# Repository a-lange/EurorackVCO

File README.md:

WIP!
Not functional, might pick this up later or replace the core of the oscillator!
As my first layout project, I bit over more than I could chew.

# EurorackVCO
Clone of Befaco 'even' VCO, original files (accessed 2025-12-12):
https://befaco.org/docs/Even_VCO/

The original pcb states that the design is public domain. Their website says CC-NC-SA.

This projects goal is to remake the 'Even VCO' in a 8hp format, to be ordered on a PCBA service like JLCPCB.
Files are (for now) easyeda pro.

First prototypes has been ordered

Sorry about the ugly pictures:

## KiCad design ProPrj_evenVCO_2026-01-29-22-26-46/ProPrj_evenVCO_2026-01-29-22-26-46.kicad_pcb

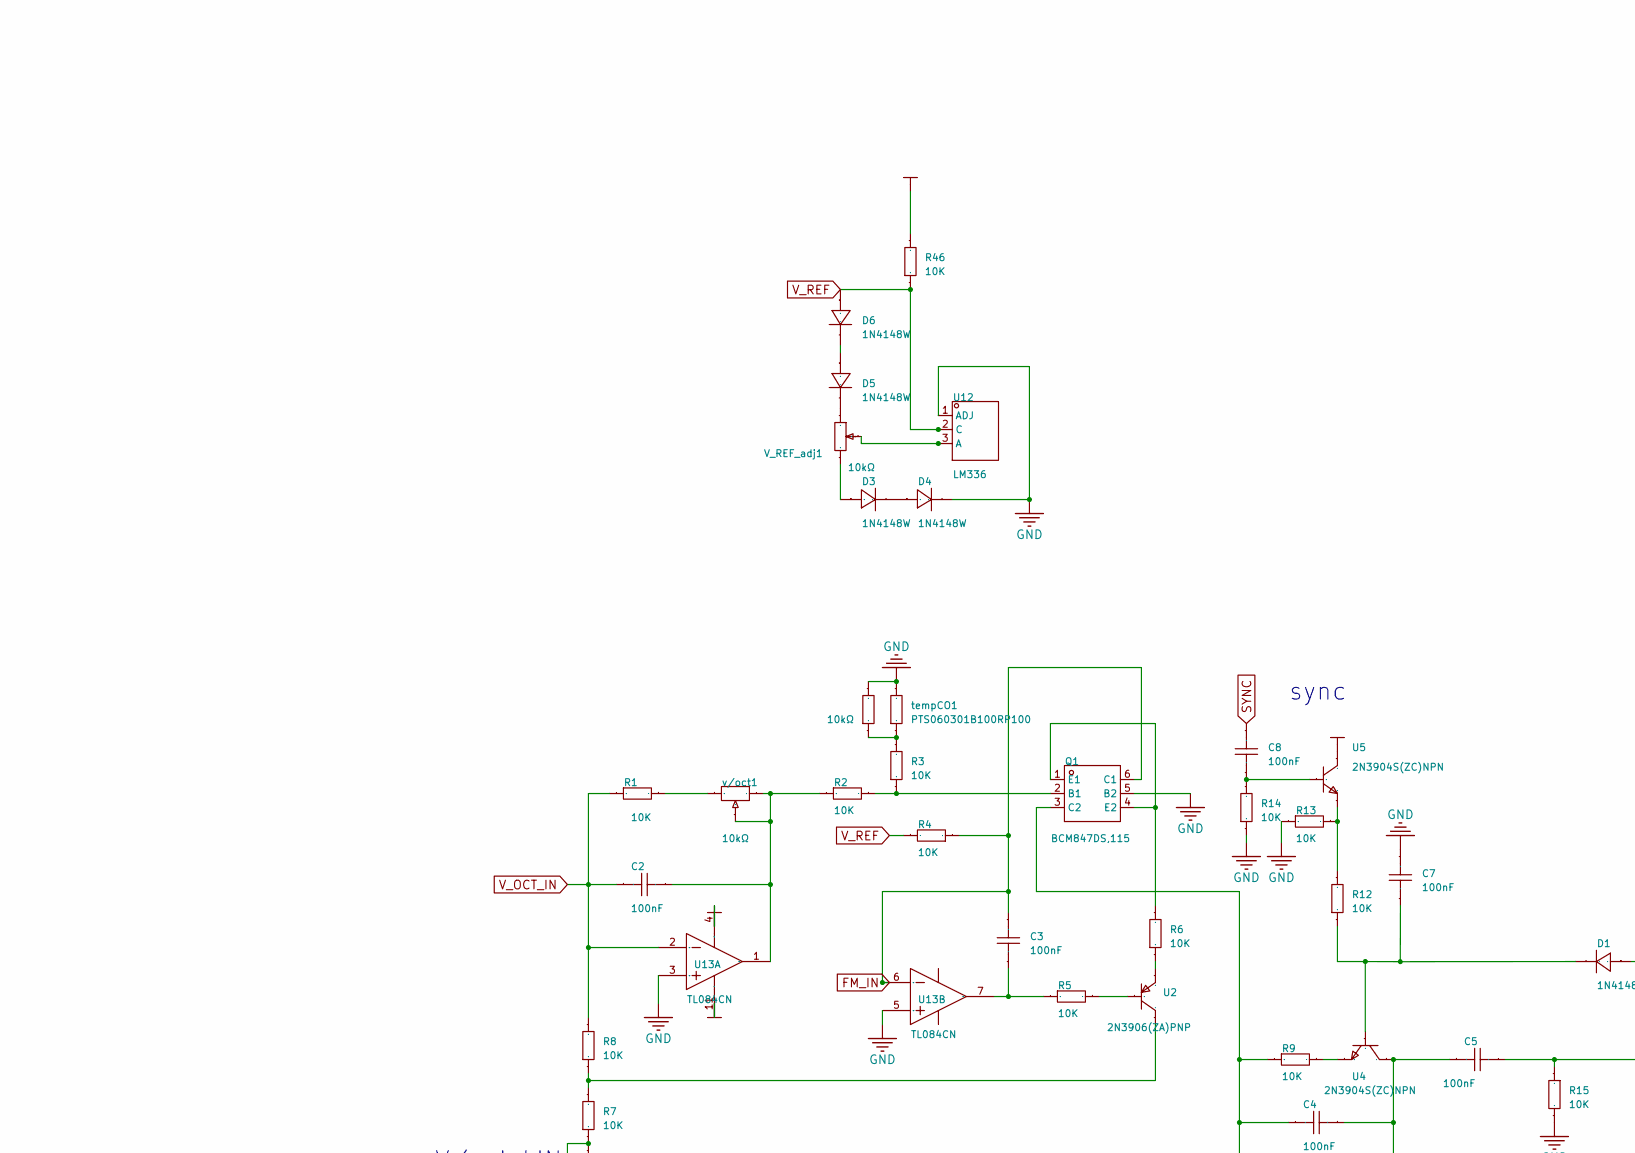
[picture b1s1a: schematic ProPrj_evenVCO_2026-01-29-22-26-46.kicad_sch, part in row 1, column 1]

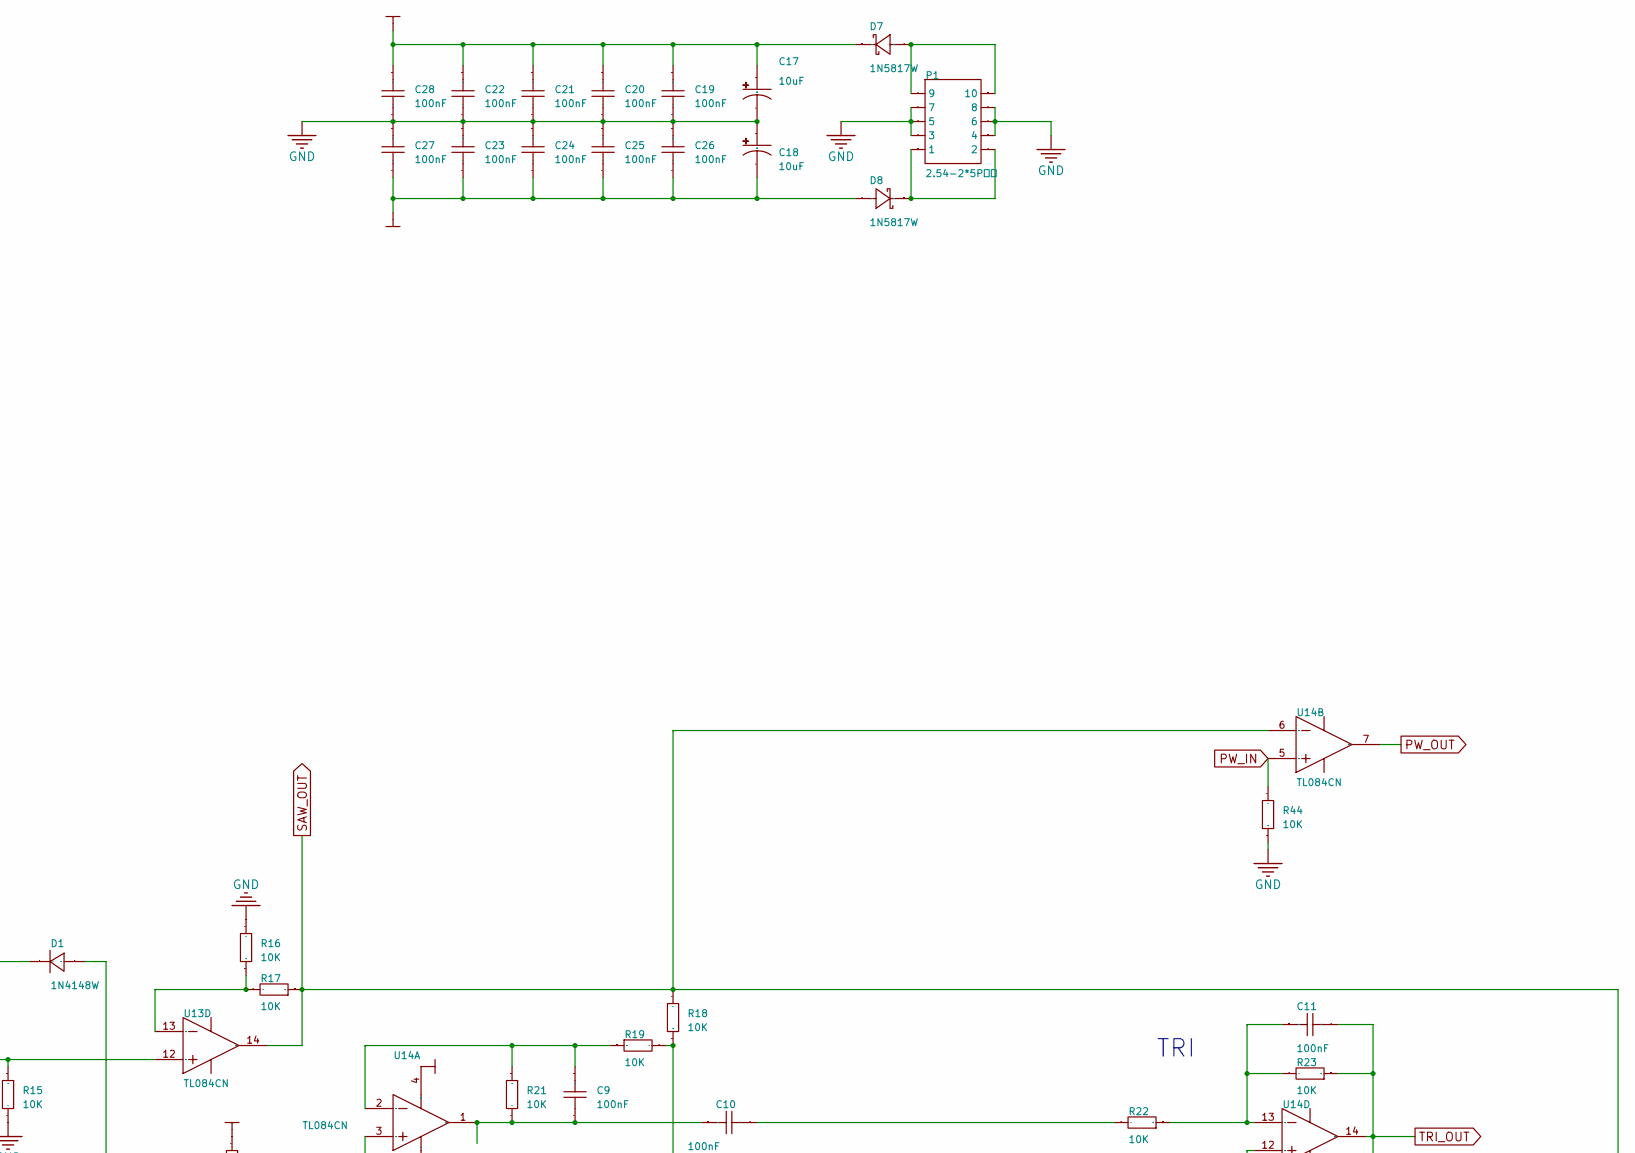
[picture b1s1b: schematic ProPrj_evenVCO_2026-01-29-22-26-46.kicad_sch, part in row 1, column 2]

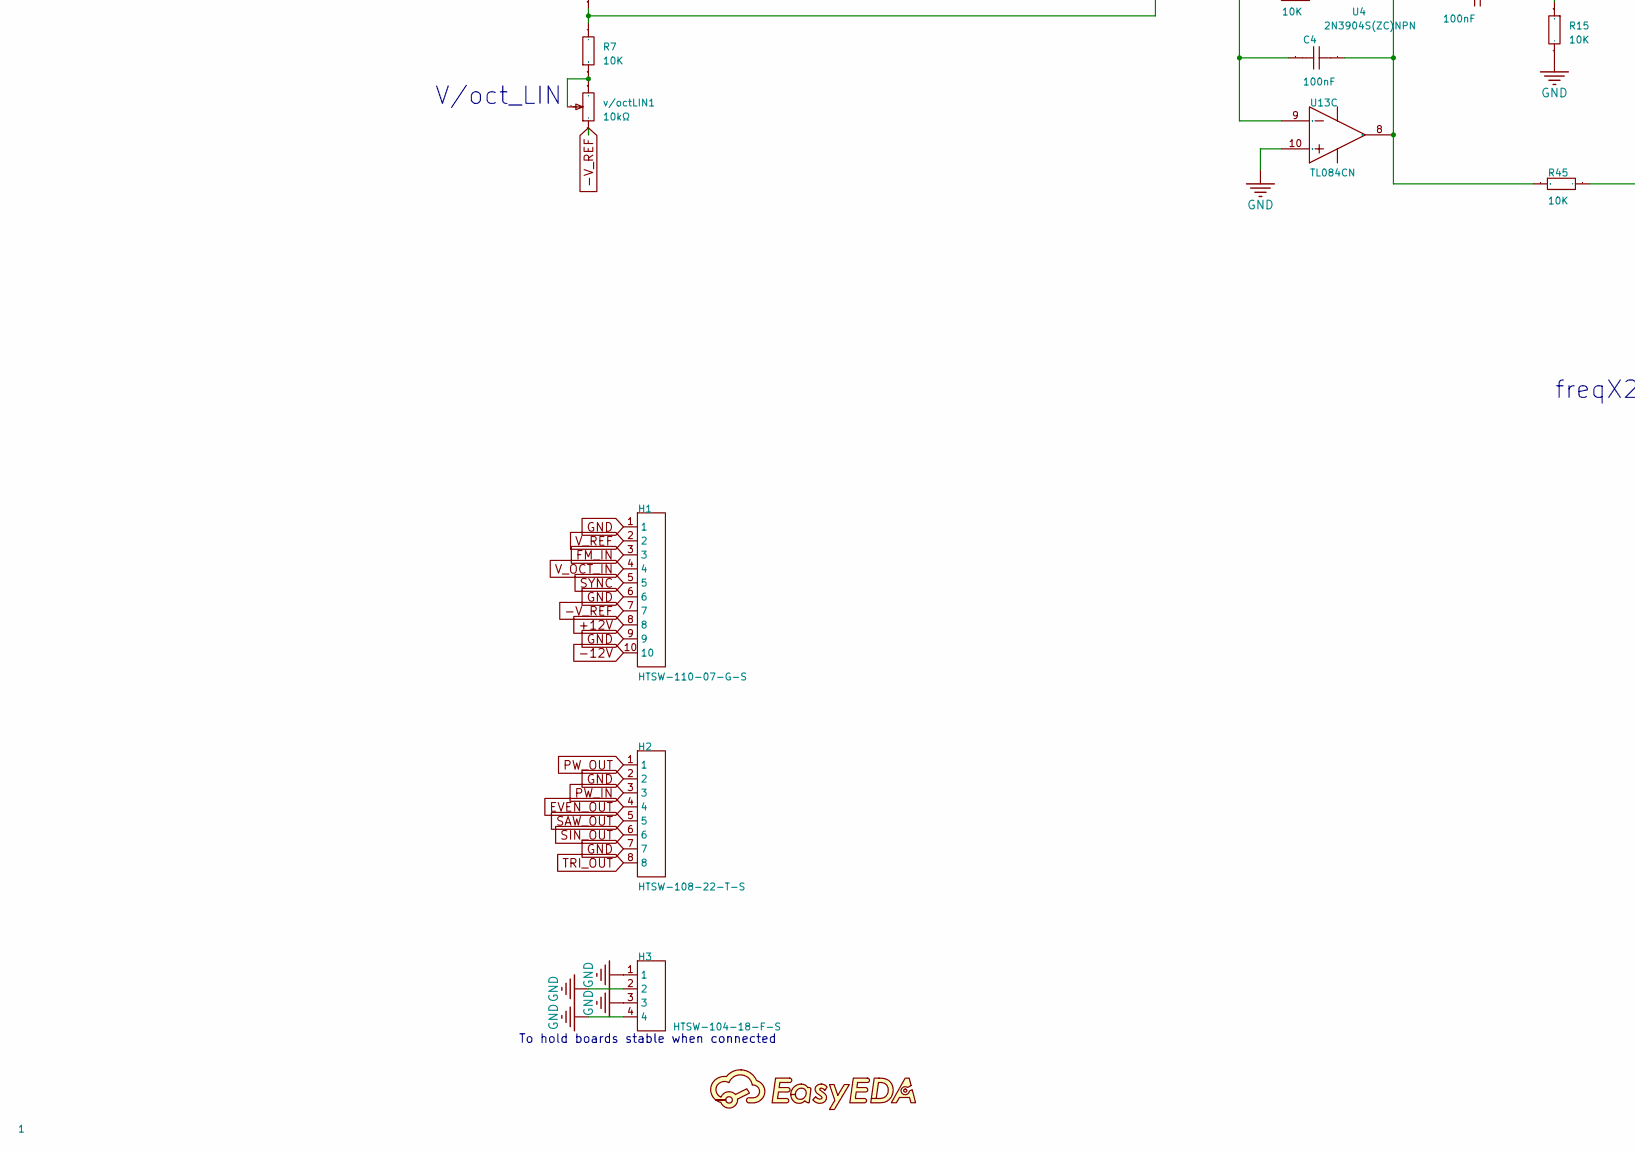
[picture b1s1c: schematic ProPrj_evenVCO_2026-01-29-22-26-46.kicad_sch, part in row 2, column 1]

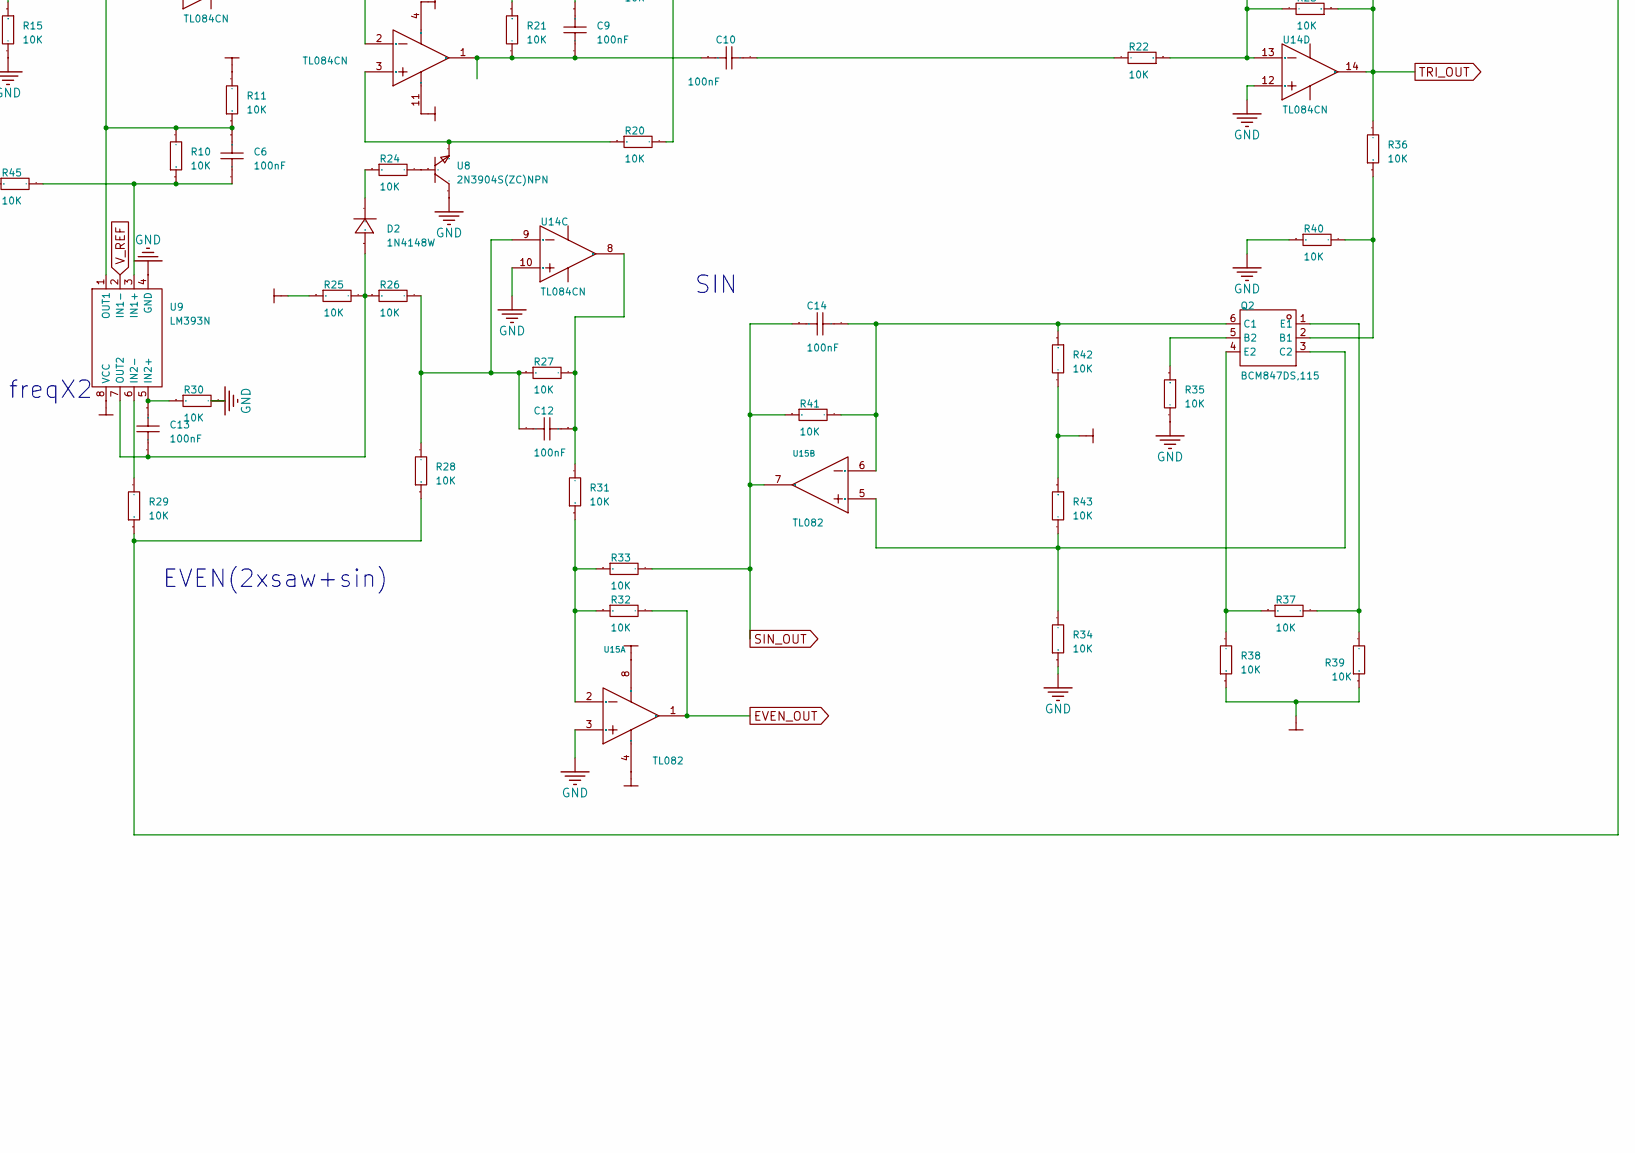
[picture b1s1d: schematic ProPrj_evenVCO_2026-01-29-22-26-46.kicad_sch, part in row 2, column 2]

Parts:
1: (no value)
C2, C3, C4, C5, C6, C7, C8, C9, C10, C11, C12, C13, C14, C19, C20, C21, C22, C23, C24, C25, C26, C27, C28: 100nF; C0805
C17, C18: 10uF; CAP-TH_BD10.0-P5.00-D1.0-FD-H16.0; Manufacturer Part 450BXW10MEFR10X16; LCSC Part Name 10uF ±20% 450V
D1, D2, D3, D4, D5, D6: 1N4148W; DO-35_BD2.0-L4.2-P8.20-D0.5-R-RD; Manufacturer Part 1N4148W; LCSC Part Name 1N4148W
D7, D8: 1N5817W; DO-41_BD2.4-L4.7-P8.70-D0.8-RD; Manufacturer Part 1N5817W; LCSC Part Name 电压:20V 电流:1A
H1: HTSW-110-07-G-S; HDR-TH_TSW-110-17-F-S-LL; Manufacturer Part HTSW-110-07-G-S; LCSC Part Name 间距:2.54mm 直插
H2: HTSW-108-22-T-S; HDR-TH_HTSW-108-22-T-S; Manufacturer Part HTSW-108-22-T-S; LCSC Part Name 间距:2.54mm 直插
H3: HTSW-104-18-F-S; HDR-TH_HTSW-104-25-S-S-LL; Manufacturer Part HTSW-104-18-F-S; LCSC Part Name 间距:2.54mm 直插
P1: 2.54-2*5P简牛; IDC-TH_10P-P2.54_C5665; Manufacturer Part power; LCSC Part Name 2.54mm 2x5P 排数:2 每排P数:5
Q1, Q2: BCM847DS,115; SC-74-6_L2.9-W1.5-P0.95-LS2.8-BR; Manufacturer Part BCM847DS,115; LCSC Part Name NPN 电流:100mA 电压:45V
R1, R2, R3, R4, R5, R6, R7, R8, R9, R10, R11, R12, R13, R14, R15, R16, R17, R18, R19, R20, R21, R22, R23, R24, R25, R26, R27, R28, R29, R30, R31, R32, R33, R34, R35, R36, R37, R38, R39, R40, R41, R42, R43, R44, R45, R46: 10K; R0805
RTemp1: 10kΩ; R0805
U2: 2N3906(ZA)PNP; SOT-23-3_L2.9-W1.3-P0.95-LS2.4-BR; Manufacturer Part 2N3906(ZA)PNP; LCSC Part Name 2N3906(ZA)PNP
U4, U5, U8: 2N3904S(ZC)NPN; SOT-23-3_L2.9-W1.3-P0.95-LS2.4-BR; Manufacturer Part 2N3904S(ZC)NPN; LCSC Part Name 2N3904S(ZC)NPN
U9: LM393N; DIP-8_L9.7-W6.4-P2.54-LS7.6-BL; Manufacturer Part LM393N; LCSC Part Name 双路差分比较器
U12: LM336; TO-92-3_L4.9-W3.7-P1.27-L; Manufacturer Part LM336; LCSC Part Name LM336
U13, U14: TL084CN; SOIC-14_L8.7-W3.9-P1.27-LS6.0-BL; Manufacturer Part TL084CN; LCSC Part Name JFET输入运算放大器
U15: TL082; SOP-8_L4.9-W3.9-P1.27-LS6.0-BL; Manufacturer Part TL082; LCSC Part Name TL082
V_REF_adj1: 10kΩ; RES-ADJ-TH_3P-L10.0-W10.0-P2.50-L
tempCO1: PTS060301B100RP100; R0805; Manufacturer Part PTS060301B100RP100; LCSC Part Name 铂金SMD扁平芯片温度传感器
v/oct1: 10kΩ; RES-ADJ-TH_3P_L9.6-W4.8-P2.50-L; Manufacturer Part CT-94EW103; LCSC Part Name 10kΩ ±10%
v/octLIN1: 10kΩ; RES-ADJ-TH_3P-L10.0-W10.0-P2.50-L

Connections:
$1N507: R1.2, v/oct1.3; also elsewhere on the board
$1N1389: C3.1, R5.1, U13.7 (OUT2)
$1N1507: R5.2, U2.2 (B)
$1N1586: R6.1, U2.1 (E)
$1N1640: R7.2, R8.1, U2.3 (C)
$1N1719: R7.1, v/octLIN1.1, v/octLIN1.2; also elsewhere on the board
$1N2016: C4.1, Q1.3 (C2), R9.1, U13.9 (IN3-)
$1N2204: R9.2, U4.2 (E)
$1N2447: C6.1, D1.1 (A), R10.2, R11.1, U9.1 (OUT1)
$1N2683: C5.1, R15.1, U13.12 (IN4+)
$1N2690: R3.2, RTemp1.1, tempCO1.1; also elsewhere on the board
$1N2936: Q1.1 (E1), Q1.4 (E2), R6.2
$1N2959: Q1.2 (B1), R2.2, R3.1
$1N3116: C4.2, C5.2, R45.1, U4.3 (C), U13.8 (OUT3)
$1N3938: C8.2, R14.2, U5.1 (B)
$1N3981: R12.2, R13.2, U5.2 (E)
$1N4358: R16.1, R17.2, U13.13 (IN4-)
$1N4747: R20.1, U8.2 (E), U14.3 (IN1+)
$1N4955: R18.1, R19.2, R20.2
$1N5308: C11.1, R22.1, R23.2, U14.13 (IN4-)
$1N5674: R24.2, U8.1 (B)
$1N5714: D2.2 (C), R24.1
$1N6127: C6.2, R10.1, R45.2, U9.3 (IN1+)
$1N6419: R29.2, U9.6 (IN2-)
$1N6424: C13.1, R30.1, U9.5 (IN2+)
$1N6566: C13.2, D2.1 (A), R25.2, R26.1, U9.7 (OUT2)
$1N7314: Q2.2 (B1), R36.1, R40.2
$1N7370: Q2.4 (E2), R37.1, R38.2
$1N7375: Q2.1 (E1), R37.2, R39.2
$1N8230: D3.1 (A), V_REF_adj1.1; also elsewhere on the board
$1N8312: U12.3 (A); also elsewhere on the board
$1N8440: D3.2 (C), D4.1 (A)
$1N8647: D5.1 (A), D6.2 (C)
$1N8687: D5.2 (C), V_REF_adj1.3; also elsewhere on the board
$1N9074: D8.1 (K), P1.1, P1.2
$1N9101: D7.2 (A), P1.9, P1.10
$1N9891: C2.1, R2.1, U13.1 (OUT1), v/oct1.1, v/oct1.2; also elsewhere on the board
$1N10311: C9.2, C10.1, R21.2, U14.1 (OUT1)
$1N10325: C9.1, R19.1, R21.1, U14.2 (IN1-)
$1N10403: C12.2, R26.2, R27.1, R28.2, U14.9 (IN3-)
$1N10523: C10.2, R22.2
$1N10728: Q2.3 (C2), R34.2, R43.2, U15.5 (2IN+)
$1N10768: C14.2, Q2.6 (C1), R41.2, R42.1, U15.6 (2IN-)
$1N10882: R31.1, R32.1, R33.1, U15.2 (1IN-)
$1N10889: C12.1, R27.2, R31.2, U14.8 (OUT3)
$1N11135: Q2.5 (B2), R35.1
+12V: C17.1, C19.1, C20.1, C21.1, C22.1, C28.1, D7.1 (K), H1.8, R11.2, R25.1, R42.2, R43.1, R46.2, U5.3 (C), U9.8 (VCC), U13.4 (VCC+), U14.4 (VCC+), U15.8 (VCC+)
-12V: C18.2, C23.2, C24.2, C25.2, C26.2, C27.2, D8.2 (A), H1.10, R38.1, R39.1, U13.11 (VCC-), U14.11 (VCC-), U15.4 (VCC-)
-V_REF: H1.7, v/octLIN1.3; also elsewhere on the board
EVEN_OUT: H2.4, R32.2, U15.1 (1OUT)
FM_IN: C3.2, H1.3, Q1.6 (C1), R4.1, U13.6 (IN2-)
GND: C7.1, C17.2, C18.1, C19.2, C20.2, C21.2, C22.2, C23.1, C24.1, C25.1, C26.1, C27.1, C28.2, D4.2 (C), H1.1, H1.6, H1.9, H2.2, H2.7, H3.1, H3.2, H3.3, H3.4, P1.3, P1.4, P1.5, P1.6, P1.7, P1.8, Q1.5 (B2), R13.1, R14.1, R15.2, R16.2, R30.2, R34.1, R35.2, R40.1, R44.1, RTemp1.2, U8.3 (C), U9.4 (GND), U12.1 (ADJ), U13.3 (IN1+), U13.5 (IN2+), U13.10 (IN3+), U14.10 (IN3+), U14.12 (IN4+), U15.3 (1IN+), tempCO1.2; also elsewhere on the board
PW_IN: H2.3, R44.2, U14.5 (IN2+)
PW_OUT: H2.1, U14.7 (OUT2)
SAW_OUT: H2.5, R17.1, R18.2, R28.1, R29.1, U13.14 (OUT4), U14.6 (IN2-)
SIN_OUT: C14.1, H2.6, R33.2, R41.1, U15.7 (2OUT)
SYNC: C8.1, H1.5
TRI_OUT: C11.2, H2.8, R23.1, R36.2, U14.14 (OUT4)
V_OCT_IN: C2.2, H1.4, R1.1, R8.2, U13.2 (IN1-)
V_REF: D6.1 (A), H1.2, R4.2, R46.1, U9.2 (IN1-), U12.2 (C)

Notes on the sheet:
freqX2
To hold boards stable when connected
sync
V/oct_LIN
SIN
TRI
EVEN(2xsaw+sin)

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
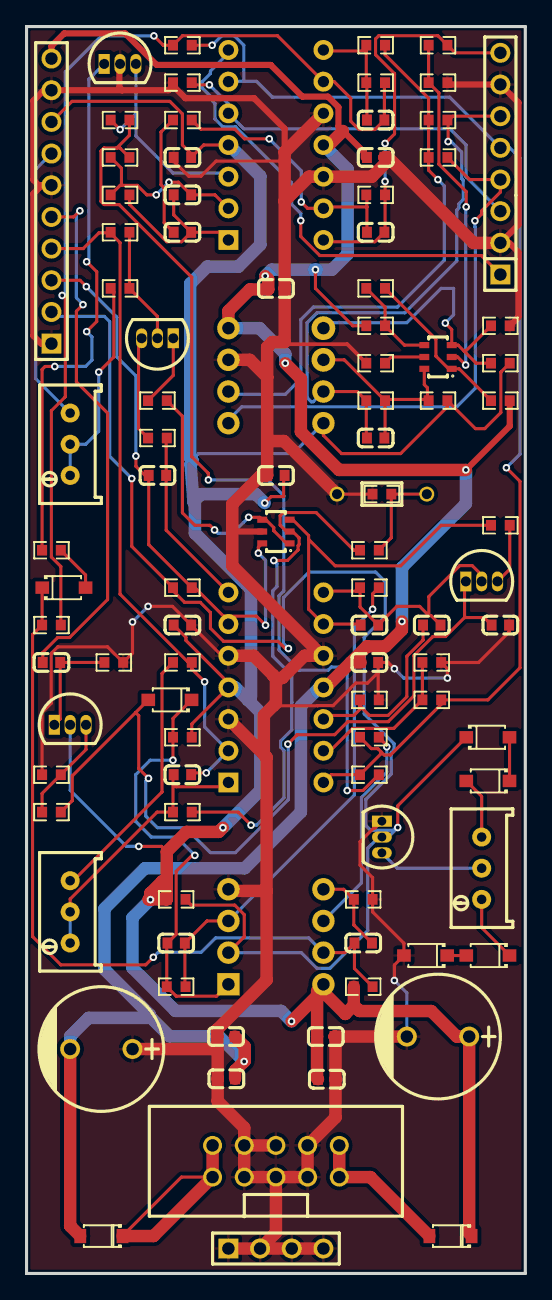
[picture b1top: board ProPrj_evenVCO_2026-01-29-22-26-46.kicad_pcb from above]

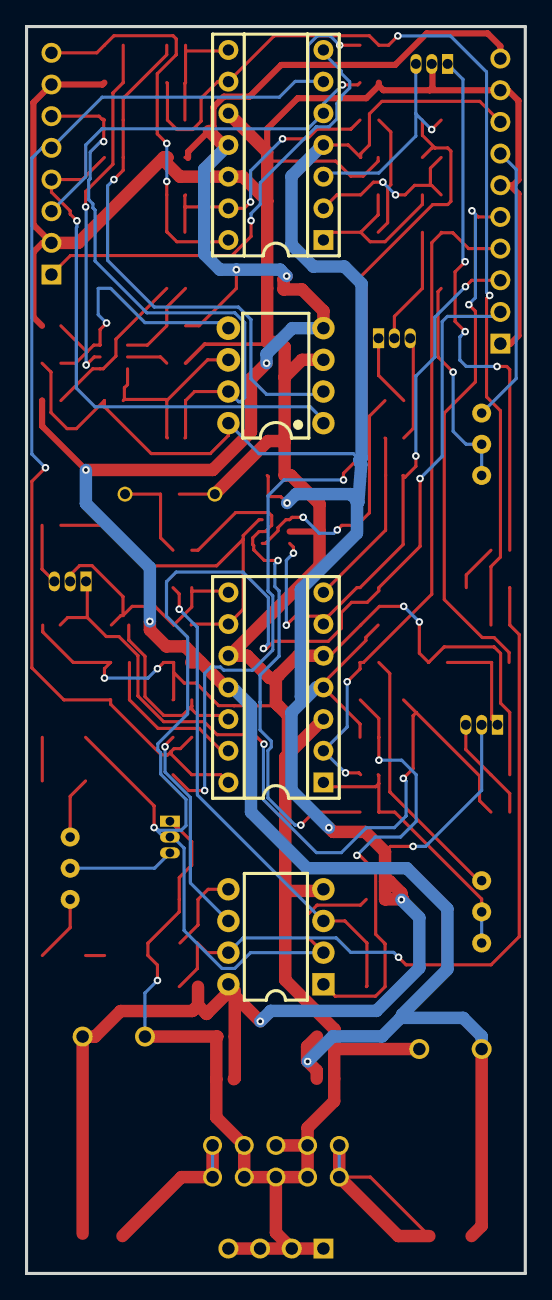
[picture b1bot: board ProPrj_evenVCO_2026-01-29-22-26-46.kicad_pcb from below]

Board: 2 copper layers, 40.0 x 100.0 mm, 99 parts (4 on the bottom side), 61 nets.

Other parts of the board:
RTemp: RES-TH_BD1.8-L3.2-P7.20-D0.4
V_REF_adj: RES-ADJ-TH_3P-L10.0-W10.0-P2.50-L
tempCO: R0603
v/oct: RES-ADJ-TH_3P-L10.0-W10.0-P2.50-L
v/octLIN: RES-ADJ-TH_3P-L10.0-W10.0-P2.50-L

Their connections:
$1N507: v/oct.3; also elsewhere on the board
$1N1719: v/octLIN.1, v/octLIN.2; also elsewhere on the board
$1N2690: RTemp.1, tempCO.1; also elsewhere on the board
$1N8230: V_REF_adj.1; also elsewhere on the board
$1N8312: V_REF_adj.2; also elsewhere on the board
$1N8687: V_REF_adj.3; also elsewhere on the board
$1N9891: v/oct.1, v/oct.2; also elsewhere on the board
-V_REF: v/octLIN.3; also elsewhere on the board
GND: RTemp.2, tempCO.2; also elsewhere on the board

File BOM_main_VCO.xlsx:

grayed out=preplaced components
No. | Quantity | Comment | Designator | Footprint | Value | Supplier Part
1 | 1 | 10nF | C2 | C0603 | 10nF | C282732
2 | 2 | 1nF | C3,C8 | C0603 | 1nF | C282732
3 | 1 | 2.2nF styrene | C4 | C0603 | 2.2nF styrene | C282732
4 | 1 | 680nF polyester | C5 | C0603 | 680nF polyester | C282732
5 | 2 | 47pF | C6,C7 | C0603 | 47pF | C282732
6 | 1 | 3pF | C9 | C0603 | 3pF | C282732
7 | 1 | 680nF | C10 | C0603 | 680nF | C282732
8 | 3 | 10pF | C11,C12,C13 | C0603 | 10pF | C282732
9 | 1 | 2.2nF | C14 | C0603 | 2.2nF | C282732
10 | 2 | 10uF | C17,C18 | CAP-TH_BD10.0-P5.00-D1.0-FD-H16.0 | 10uF | C473172
11 | 10 | 100nF | C19,C20,C21,C22,C23,C24,C25,C26,C27,C28 | C0603 | 100nF | C282732
12 | 6 | 1N4148W | D1,D2,D3,D4,D5,D6 | SOD-123F_L2.7-W1.6-LS3.8-RD |  | C81598
13 | 2 | 1N5817W | D7,D8 | SOD-123_L2.8-W1.8-LS3.7-RD |  | C7473302
14 | 1 | HTSW-110-07-G-S | H1 | HDR-TH_TSW-110-17-F-S-LL |  | C7286348
15 | 1 | HTSW-108-22-T-S | H2 | HDR-TH_HTSW-108-22-T-S |  | C6877799
16 | 1 | HTSW-104-18-F-S | H3 | HDR-TH_HTSW-104-25-S-S-LL |  | C7286115
17 | 1 | power | P1 | IDC-TH_10P-P2.54_C5665 |  | C5665
18 | 2 | BCM847DS,115 | Q1,Q2 | SC-74-6_L2.9-W1.5-P0.95-LS2.8-BR |  | C549558
19 | 1 | 95.3k | R1 | R0603 | 95.3k | C141518
20 | 1 | 6.2k | R2 | R0603 | 6.2k | C141518
21 | 1 | 4.22R | R3 | R0603 | 4.22R | C141518
22 | 1 | 820k | R4 | R0603 | 820k | C141518
23 | 2 | 1.5k | R5,R6 | R0603 | 1.5k | C141518
24 | 1 | 510R | R7 | R0603 | 510R | C141518
25 | 1 | 150k | R8 | R0603 | 150k | C141518
26 | 1 | 270R | R9 | R0603 | 270R | C141518
27 | 1 | 330k | R10 | R0603 | 330k | C141518
28 | 4 | 22k | R11,R12,R31,R36 | R0603 | 22k | C141518
29 | 9 | 100k | R13,R16,R17,R21,R22,R28,R29,R30,R44 | R0603 | 100k | C141518
30 | 1 | 47k | R14 | R0603 | 47k | C141518
31 | 1 | 2M | R15 | R0603 | 2M | C141518
32 | 7 | 10K | R18,R32,R34,R41,R42,R43,R45 | R0603 | 10K | C141518
33 | 1 | 82k | R19 | R0603 | 82k | C141518
34 | 1 | 100K | R20 | R0603 | 100K | C141518
35 | 1 | 200k | R23 | R0603 | 200k | C141518
36 | 2 | 220k | R24,R27 | R0603 | 220k | C141518
37 | 1 | 2.2k | R25 | R0603 | 2.2k | C141518
38 | 1 | 430k | R26 | R0603 | 430k | C141518
39 | 1 | 20k | R33 | R0603 | 20k | C141518
40 | 3 | 1k | R35,R40,R46 | R0603 | 1k | C141518
41 | 1 | 390 | R37 | R0603 | 390 | C141518
42 | 2 | 43k | R38,R39 | R0603 | 43k | C141518
43 | 1 | Res_AXIAL-1/8W | RTemp | RES-TH_BD1.8-L3.2-P7.20-D0.4
44 | 1 | PTS060301B100RP100 | tempCO | R0603 | 100R_3500ppm | C141518
45 | 1 | 2N3906(ZA)PNP | U2 | TO-92-3_L4.9-W3.7-P1.27-L_RICKY-RS0108S-U |  | C49023424
46 | 3 | 2N3904S(ZC)NPN | U4,U5,U8 | TO-92-3_L4.9-W3.7-P1.27-L_RICKY-RS0108S-U |  | C9900013034
47 | 1 | LM393N | U9 | DIP-8_L9.7-W6.4-P2.54-LS7.6-BL |  | C19708139
48 | 1 | LM336 | U12 | TO-92-3_L4.9-W3.7-P1.27-L |  | C9406
49 | 2 | TL084CN | U13,U14 | DIP-14_L17.8-W10.2-P2.54-BL_3 |  | C54501
50 | 1 | TL082 | U15 | PDIP-8_L9.6-W6.4-P2.54-LS7.6-BL |  | C9385
51 | 2 | 10kΩ | v/oct,V_REF_adj | RES-ADJ-TH_3P-L10.0-W10.0-P2.50-L | 10kΩ | C118954
52 | 1 | 1kΩ | v/octLIN | RES-ADJ-TH_3P-L10.0-W10.0-P2.50-L | 1kΩ | C118954

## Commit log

2025-12-15 Add files via upload
    Some fixes on the IO-board, reworked routes.
    Known issue: 10-pole switch has SMD-footprint, will be changed when a good switch is found.
2025-12-16 Add files via upload
    Added TH footprint(and 0805 SMD) for temperature compensation resistor.
    Reworked routing
    Changed IO-pcb to through hole components
2025-12-18 Update README.md
    Panel added
2026-01-29 Add files via upload
    Files for reference only, converted to kicad without much double checking
